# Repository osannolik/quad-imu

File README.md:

Quadcopter or general 6 DOF IMU
===========================

## Hardware

* ARM Cortex-M4, STM32F405, 168 MHz, FPU
* Accelerometer and gyro ICM20608
* 2.4 GHz Transceiver nRF24L01+
* USB Power Manager with Li-Ion charger LTC3553
* USB to serial UART interface FT232RQ

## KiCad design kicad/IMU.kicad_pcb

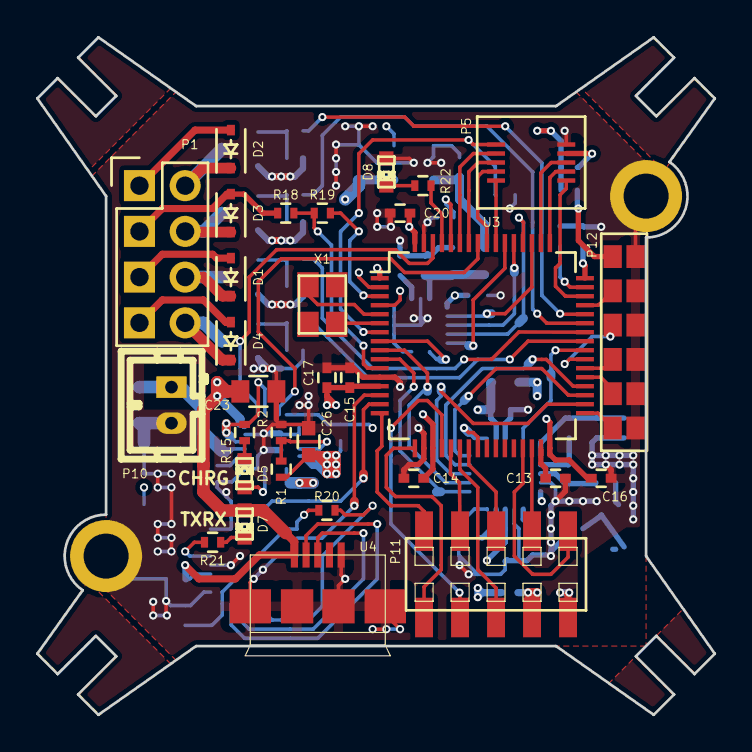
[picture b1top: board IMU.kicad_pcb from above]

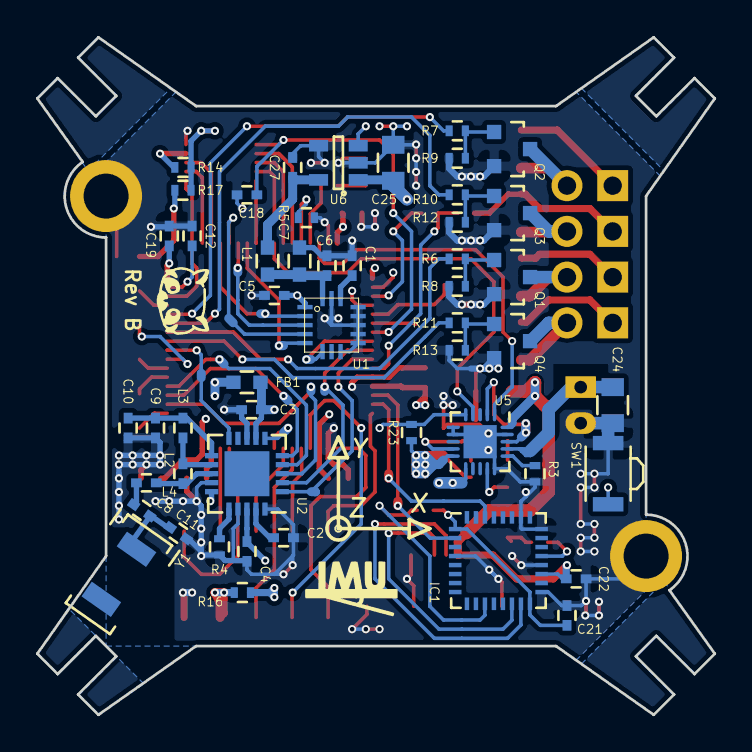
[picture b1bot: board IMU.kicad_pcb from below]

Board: 4 copper layers, 37.6 x 37.6 mm, 83 parts (50 on the bottom side), 88 nets.

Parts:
C1: 470n; C_0402
C2: 33n; C_0402
C3, C15: 10n; C_0402
C4: 1n; C_0402
C5, C6, C14, C16, C18, C19, C20, C21, C22: 100n; C_0402
C7, C26: 4u7; C_0603
C8: 1p5; C_0402
C9: 2n2; C_0402
C10: 4p7; C_0402
C11: 1p; C_0402
C12, C13: 2u2; C_0402
C17, C27: 1u; C_0402
C23, C24, C25: 10u; C_0805
D1, D2, D3, D4: BAT54WS; SOD-323
D5, D8: LED; LED-0603
D7: TXRXLED; LED-0603
FB1: 600R@100MHz; C_0603
IC1: FT232RQ; QFN-32-1EP_5x5mm_Pitch0.5mm
L1: 2u2; C_0603
L2: 8n2; C_0402
L3: 2n7; C_0402
L4: 3n9; C_0402
MH1, MH2: Mounting; MountingHole_2-5mm
P1: CONN_02X04; Pin_Header_Straight_2x04
P5: JTAG_DB; DF23C-10DP-0.5V
P10: CONN_01X02; b2b-ph-kl
P11: CONN_02X05; molexNoHole-87832-10
P12: CONN_02X06; GS_6x2
Q1, Q2, Q3, Q4: IRFML8244; SOT-23
R1: 560k; R_0402
R2: 180k; R_0402
R3: 3k6; R_0402
R4: 22k; R_0402
R5, R8, R9, R12, R13, R20: 10k; R_0402
R6, R7, R10, R11, R14, R16, R17: 100; R_0402
R15, R21, R22: 2k2; R_0402
R18, R19, R23: 100k; R_0402
SW1: SW_PUSH; B3U_3000P
U1: ICM20608; LGA16
U2: NRF24L01; QFN-20-1EP_4x4mm_Pitch0.5mm
U3: STM32F405; LQFP-64_10x10mm_Pitch0.5mm
U4: MICRO-B_USB; USB-B-Micro
U5: LTC3553; UQFN-20-1EP_3x3mm_Pitch0.4mm
U6: TLV70033; SOT-23-5
X1: 16MHz; crystal_FA238-TSX3225
Y1: CHIP_ANTENNA; ANTENNA-JOHANSON-2.45GHZ

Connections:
+5V: C22.1, C23.1, D7.2, IC1.19, U4.1, U5.20
+BATT: C24.1, D1.2, D2.2, D3.2, D4.2, P1.1, P1.3, P1.5, P1.7, P10.1, R18.1, U5.17
/Mems and Radio/MEMS_CS: U1.5, U3.54
/Mems and Radio/MEMS_INT: U1.6, U3.8
/Mems and Radio/MEMS_MISO: U1.4, U3.52
/Mems and Radio/MEMS_MOSI: U1.3, U3.53
/Mems and Radio/MEMS_SCLK: U1.2, U3.51
/Mems and Radio/NRF24_CE: U2.1, U3.10
/Mems and Radio/NRF24_CSN: U2.2, U3.9
/Mems and Radio/NRF24_IRQ: U2.6, U3.24
/Mems and Radio/NRF24_MISO: U2.5, U3.35
/Mems and Radio/NRF24_MOSI: U2.4, U3.36
/Mems and Radio/NRF24_OSC: U2.10, U3.40
/Mems and Radio/NRF24_SCK: U2.3, U3.34
/Microcontroller/CON_CLK: P11.4, U3.21
/Microcontroller/CON_DAC: P11.3, U3.20
/Microcontroller/CON_MISO: P11.5, U3.22
/Microcontroller/CON_MOSI: P11.6, U3.23
/Microcontroller/CON_RX: P11.1, U3.17
/Microcontroller/CON_SCL: P11.10, U3.29
/Microcontroller/CON_SDA: P11.8, U3.30
/Microcontroller/CON_TX: P11.2, U3.16
/Microcontroller/DB_RX: P5.3, U3.59
/Microcontroller/DB_TX: P5.5, U3.58
/Microcontroller/HPWR: U3.62, U5.1
/Microcontroller/LDO_ON: R23.2, U3.2, U5.5
/Microcontroller/M1: R6.2, U3.42
/Microcontroller/M1N: D1.1, P1.6, Q1.3
/Microcontroller/M2: R10.2, U3.43
/Microcontroller/M2N: D3.1, P1.4, Q3.3
/Microcontroller/M3: R7.2, U3.44
/Microcontroller/M3N: D2.1, P1.2, Q2.3
/Microcontroller/M4: R11.2, U3.41
/Microcontroller/M4N: D4.1, P1.8, Q4.3
/Microcontroller/NJTRST: P5.7, U3.56
/Microcontroller/NRST: C18.1, P5.1, U3.7
/Microcontroller/PAD1: P12.3, U3.45
/Microcontroller/PAD2: P12.5, U3.39
/Microcontroller/PAD3: P12.7, U3.38
/Microcontroller/PAD4: P12.9, U3.37
/Microcontroller/PAD5: P12.11, U3.33
/Microcontroller/PWREN#: IC1.11, R20.2, U3.4
/Microcontroller/TCK/SWDCLK: P5.8, U3.49
/Microcontroller/TDI: P5.6, U3.50
/Microcontroller/TDO/SWO: P5.9, U3.55
/Microcontroller/TMS/SWDIO: P5.10, U3.46
/Microcontroller/VBAT: R18.2, R19.1, U3.11
/Microcontroller/VBAT0: R19.2, U3.3
/Microcontroller/~ON: SW1.2, U3.57, U5.4
/Power/FTDI_RXD: IC1.2, U3.14
/Power/FTDI_TXD: IC1.30, U3.15
/Power/VccIO: C21.1, IC1.1, IC1.16, R20.1
/Power/Vout: C25.1, R15.1, U5.2, U5.11, U5.18, U6.1, U6.3
GND: C1.2, C2.2, C3.2, C4.2, C5.2, C6.2, C7.2, C9.2, C10.2, C11.1, C12.2, C13.2, C14.2, C15.2, C16.2, C17.2, C18.2, C19.2, C20.2, C21.2, C22.2, C23.2, C24.2, C25.2, C26.2, C27.2, D8.2, IC1.4, IC1.17, IC1.20, IC1.24, IC1.26, MH1.1, MH2.1, P5.2, P10.2, P11.9, P12.2, P12.4, P12.6, P12.8, P12.10, P12.12, Q1.2, Q2.2, Q3.2, Q4.2, R2.2, R3.2, R4.2, R5.1, R8.2, R9.2, R12.2, R13.2, SW1.1, U1.8, U1.9, U1.10, U1.11, U1.12, U1.13, U1.15, U2.8, U2.14, U2.17, U2.20, U3.12, U3.18, U3.63, U4.5, U5.6, U5.7, U5.15, U5.19, U5.21, U6.2, U6.4
unnamed: C1.1, U1.14
unnamed: C2.1, U2.19
unnamed: C3.1, C4.1, FB1.1, U2.7, U2.15, U2.18
unnamed: C6.1, C7.1, L1.2, U1.16
unnamed: C8.2, L4.2
unnamed: C9.1, C10.1, L3.2, U2.11
unnamed: C8.1, C11.2, Y1.1
unnamed: C12.1, U3.47
unnamed: C13.1, U3.31
unnamed: D5.1, R15.2
unnamed: D5.2, U5.14
unnamed: D7.1, R21.1
unnamed: D8.1, R22.2
unnamed: IC1.14, U4.3
unnamed: IC1.15, U4.2
unnamed: IC1.21, R21.2
unnamed: L2.1, L3.1, U2.12
unnamed: L2.2, L4.1, U2.13
unnamed: P5.4, R14.1
unnamed: P11.7, R16.2
unnamed: P12.1, R17.2
unnamed: Q1.1, R6.1, R8.1
unnamed: Q2.1, R7.1, R9.1
unnamed: Q3.1, R10.1, R12.1
unnamed: Q4.1, R11.1, R13.1
unnamed: R1.2, R2.1, U5.9
unnamed: R3.1, U5.16
unnamed: R4.1, U2.16
unnamed: R5.2, U3.60
unnamed: R22.1, U3.61
unnamed: U3.5, X1.2
unnamed: U3.6, X1.1
VAA: C27.1, L1.1, U6.5
VDD: C5.1, C14.1, C15.1, C16.1, C17.1, C19.1, C20.1, C26.1, FB1.2, R1.1, R14.2, R16.1, R17.1, R23.1, U1.1, U3.1, U3.13, U3.19, U3.32, U3.48, U3.64, U5.10

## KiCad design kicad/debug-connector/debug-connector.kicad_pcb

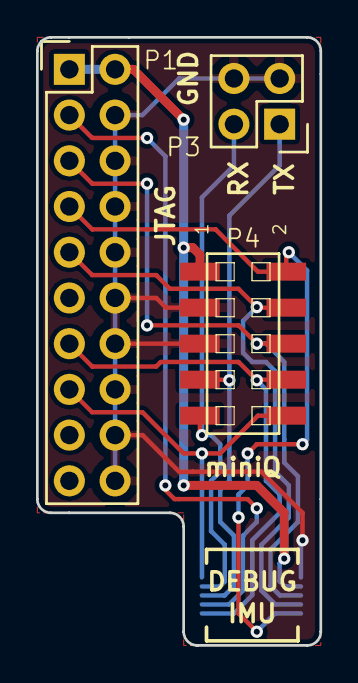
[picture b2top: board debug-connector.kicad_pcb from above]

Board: 2 copper layers, 15.7 x 33.8 mm, 4 parts (1 on the bottom side), 10 nets.

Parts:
P1: CONN_02X10; Pin_Header_Straight_2x10
P2: CONN_02X05; DF23C-10DS-0.5V
P3: CONN_01X04; Pin_Header_Straight_2x02
P4: CONN_02X05; molexNoHole-87832-10

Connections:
/NRST: P1.15, P2.9, P4.10
/TCK_SWCLK: P1.9, P2.4, P4.4
/TDI: P1.5, P2.6, P4.6
/TDO_SWO: P1.13, P2.1, P4.8
/TMS_SWDIO: P1.7, P2.2, P4.2
/TRST: P1.3, P2.3
/UART_RX: P2.7, P3.2, P4.9
/UART_TX: P2.5, P3.1, P4.7
/VAPP: P1.1, P1.2, P2.8, P4.1
GND: P1.4, P1.6, P1.8, P1.10, P1.12, P1.14, P1.16, P1.18, P1.20, P2.10, P3.3, P3.4, P4.3, P4.5

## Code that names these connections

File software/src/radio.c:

/*
 * radio.c
 *
 *  Created on: 15 nov 2015
 *      Author: osannolik
 */


#include "radio.h"
#include "com.h"
#include "queue.h"
#include "stm32f4xx_hal.h"
#include "nrf24.h"

#define MIN(X,Y) ((X)<(Y)?(X):(Y))

static radio_DataTypeDef radio_data = RADIO_DATA_INIT;

static uint8_t radio_ByteBufRx[RADIO_BUF_RX_LEN];

uint32_t radio_receive_data(uint8_t **data)
{
  uint8_t *buf_ptr = radio_ByteBufRx;

  while (!nRF24_RxFifoEmpty())
    buf_ptr += nRF24_RxData(buf_ptr);

  *data = radio_ByteBufRx;

  return (buf_ptr - radio_ByteBufRx);
}

uint32_t radio_send_data(uint8_t* data, uint16_t len)
{
  uint16_t len_to_send;
  uint8_t *from_address, *next_address = data;

  if (nRF24_TxFifoFull()) {
    if (++radio_data.tx_fifo_full_cntr < RADIO_TX_FIFO_FULL_CNTR_MAX) {
      return 0;
    } else {
      nRF24_TxFifoFlush();
      radio_data.tx_fifo_full_cntr = 0;
    }
  }

  do {
    len_to_send = MIN(len, nRF24_TX_DATA_LEN_MAX);
    from_address = next_address;
    len -= len_to_send;
    next_address += len_to_send;
  } while (len_to_send && !(nRF24_TxData(from_address, len_to_send) & nRF24_FIFO_STATUS_TX_FULL));

  return (uint32_t) (next_address - data);
}

int radio_init()
{
  int err = 0;

  err |= radio_init_io();
  err |= radio_init_peripheral();

  if (err)
    return -1;

  nRF24_SettingsTypeDef nRF24_settings;

  nRF24_settings.TxRxMode = PRIMARY_TX;
  uint8_t a;
  for (a=0; a<nRF24_ADR_LEN; a++)
    nRF24_settings.TX_ADR[a] = 0xE7;
  nRF24_settings.InterruptCallback = NULL;

  radio_data.is_init = 1;

  return nRF24_init(&nRF24_settings);
}

int radio_init_peripheral()
{
  // Enable oscillator output
  HAL_RCC_MCOConfig(RCC_MCO2, RCC_MCO2SOURCE_HSE, RCC_MCODIV_1);
  //__HAL_RCC_SPI1_CLK_ENABLE();
  __HAL_RCC_SPI2_CLK_ENABLE();

  // SPI
  SPI_HandleTypeDef SPIhandle;
  //SPIhandle.Init.BaudRatePrescaler = SPI_BAUDRATEPRESCALER_16;
  SPIhandle.Init.BaudRatePrescaler = SPI_BAUDRATEPRESCALER_8;
  SPIhandle.Init.CLKPhase = SPI_PHASE_1EDGE;
  SPIhandle.Init.CLKPolarity = SPI_POLARITY_LOW;
  SPIhandle.Init.CRCCalculation = SPI_CRCCALCULATION_DISABLED;
  SPIhandle.Init.DataSize = SPI_DATASIZE_8BIT;
  SPIhandle.Init.Direction = SPI_DIRECTION_2LINES;
  SPIhandle.Init.FirstBit = SPI_FIRSTBIT_MSB;
  SPIhandle.Init.Mode = SPI_MODE_MASTER;
  SPIhandle.Init.NSS = SPI_NSS_SOFT;
  SPIhandle.Init.TIMode = SPI_TIMODE_DISABLED;
  SPIhandle.Instance = nRF24_SPI_INSTANCE;

  HAL_SPI_Init(&SPIhandle);
  __HAL_SPI_ENABLE(&SPIhandle);

  return 0;
}

int radio_init_io()
{
  GPIO_InitTypeDef GPIOinitstruct;

  __HAL_RCC_GPIOB_CLK_ENABLE();
  __HAL_RCC_GPIOC_CLK_ENABLE();

  //__HAL_RCC_GPIOA_CLK_ENABLE();

  // MOSI
  GPIOinitstruct.Pin = nRF24_MOSI_PIN;
  GPIOinitstruct.Speed = GPIO_SPEED_HIGH;
  GPIOinitstruct.Pull = GPIO_PULLUP;
  GPIOinitstruct.Mode = GPIO_MODE_AF_PP;
  //GPIOinitstruct.Alternate = GPIO_AF5_SPI1;
  GPIOinitstruct.Alternate = GPIO_AF5_SPI2;
  HAL_GPIO_Init(nRF24_MOSI_PORT, &GPIOinitstruct);

  // MISO
  GPIOinitstruct.Pin = nRF24_MISO_PIN;
  GPIOinitstruct.Speed = GPIO_SPEED_HIGH;
  GPIOinitstruct.Pull = GPIO_PULLUP;
  GPIOinitstruct.Mode = GPIO_MODE_AF_PP;
  //GPIOinitstruct.Alternate = GPIO_AF5_SPI1;
  GPIOinitstruct.Alternate = GPIO_AF5_SPI2;
  HAL_GPIO_Init(nRF24_MISO_PORT, &GPIOinitstruct);

  // SCK
  GPIOinitstruct.Pin = nRF24_SCK_PIN;
  GPIOinitstruct.Pull = GPIO_NOPULL;
  GPIOinitstruct.Mode = GPIO_MODE_AF_PP;
  //GPIOinitstruct.Alternate = GPIO_AF5_SPI1;
  GPIOinitstruct.Alternate = GPIO_AF5_SPI2;
  HAL_GPIO_Init(nRF24_SCK_PORT, &GPIOinitstruct);

  // CSN
  GPIOinitstruct.Pin = nRF24_CSN_PIN;
  GPIOinitstruct.Speed = GPIO_SPEED_HIGH;
  GPIOinitstruct.Pull = GPIO_PULLUP;
  GPIOinitstruct.Mode = GPIO_MODE_OUTPUT_PP;
  HAL_GPIO_Init(nRF24_CSN_PORT, &GPIOinitstruct);

  // CE
  GPIOinitstruct.Pin = nRF24_CE_PIN;
  GPIOinitstruct.Speed = GPIO_SPEED_HIGH;
  GPIOinitstruct.Pull = GPIO_NOPULL;
  GPIOinitstruct.Mode = GPIO_MODE_OUTPUT_PP;
  HAL_GPIO_Init(nRF24_CE_PORT, &GPIOinitstruct);

  // IRQ
  GPIOinitstruct.Pin = nRF24_IRQ_PIN;
  GPIOinitstruct.Speed = GPIO_SPEED_HIGH;
  GPIOinitstruct.Pull = GPIO_PULLUP;
  GPIOinitstruct.Mode = GPIO_MODE_IT_FALLING;
  HAL_GPIO_Init(nRF24_IRQ_PORT, &GPIOinitstruct);
  HAL_NVIC_SetPriority(EXTI4_IRQn, 0x0F, 0x0F);
  HAL_NVIC_EnableIRQ(EXTI4_IRQn);

  return 0;
}

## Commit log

2015-05-30 First commit. Files migrated from Dropbox.
2015-05-31 Added edge pads and some more vias.
2015-06-01 Added status LEDs to FTDI IC and bat voltage to mcu ADC.
2015-06-02 Changed LP2992 to TLV700 with better PSRR.
2015-06-02 Added TLV700 to parts list.
2015-06-02 Placed ref text on pcb.
2015-06-03 Moved USB and external edge connector and re-routed FTDI IC.
2015-06-06 Replaced USB connector footprint.
2015-06-06 Updated parts list.
2015-06-06 Added debug LED to mcu pin.
2015-06-06 Cleared corner areas to allow for arm attachments.
2015-06-07 Added shoulders for arms at corners.
2015-06-07 Fixed bug causing script not working with relative paths.
2015-06-08 Add solder pads to arm-mountings.
2015-06-09 Change clearance of power planes and add logos. Generate BOM.
2015-06-10 Connect CS of MEMS to mcu.
2015-06-11 Update BOM with pn.
2015-06-13 Add mounting holes and XYZ-silkscreen.
2015-06-13 Move panda logo.
2015-06-13 Digikey cart and oshpark gerbers added.
2015-06-13 Reorganized parts and BOM.
2015-06-21 Created debug connector receptacle footprint.
2015-06-21 Changed R,C and D's in sch from old standard lib to new lib. Move GND-via under debug connector.
2015-06-21 Work commit: Add debug connector project.
2015-06-23 First routing of debug connector pcb.
2015-06-24 Add outline and ground planes
2015-06-25 Move debug connector to right and add text and logos on silkscreen.
2015-06-27 Debug connector remade to better fit on IMU board.
2015-06-27 Add Debug connector Rev A gerbers.
2015-07-23 Corrected ON-circuitry of LTC3553, and other minor board changes.
2015-07-24 Connected mcu pin to LDO_ON.
2015-07-24 Gerbers generated for Rev B
2015-07-24 First version of quad-arms
2016-06-24 Remove unnecessary files
2016-06-26 Add embryo of software. Only basic functionality and tests implemented.
2016-06-26 Readme
2016-12-25 Better readme
